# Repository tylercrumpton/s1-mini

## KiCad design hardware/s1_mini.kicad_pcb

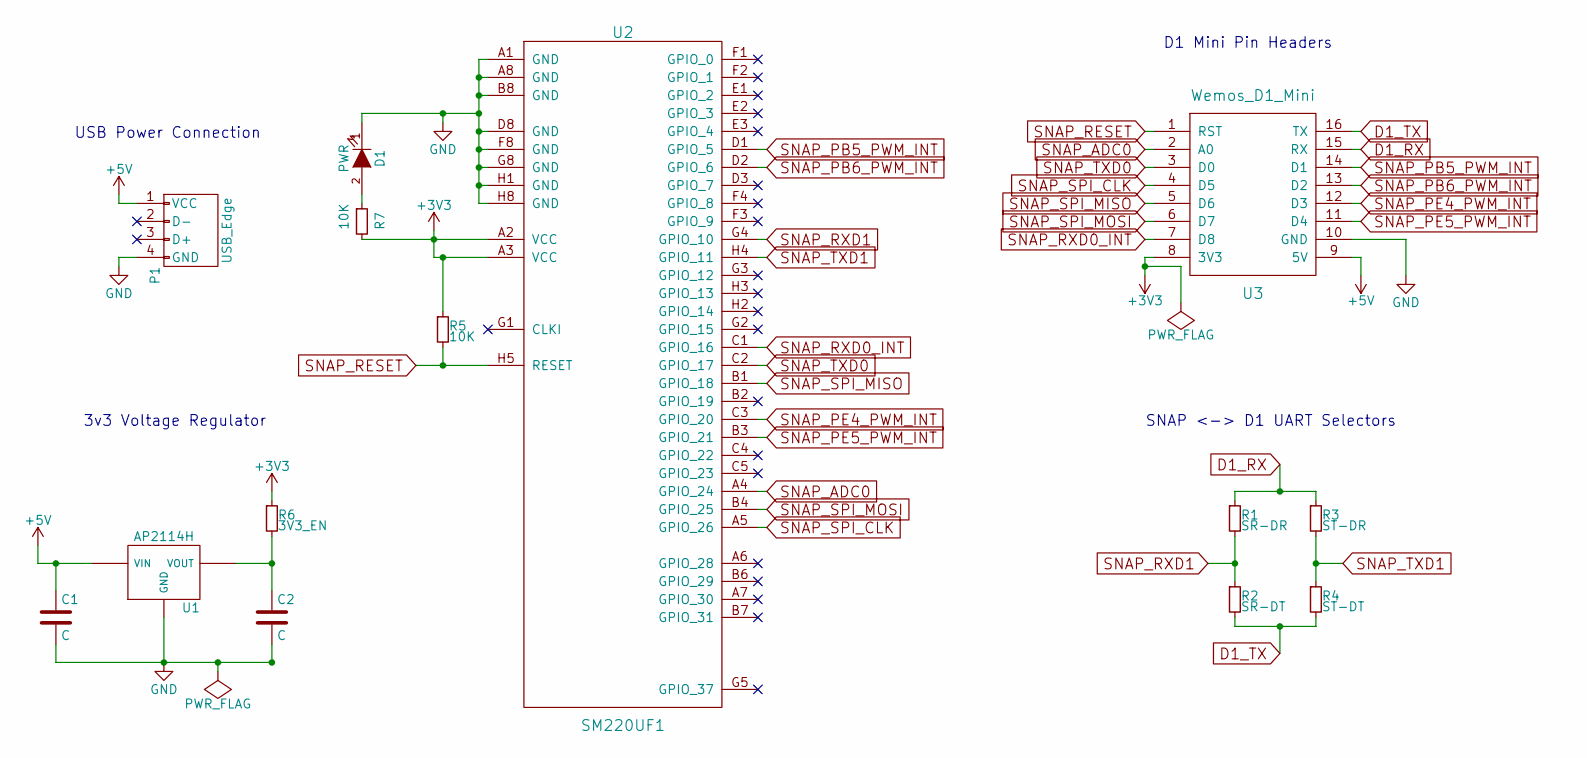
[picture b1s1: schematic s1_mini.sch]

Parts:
C1, C2: C; C_0805_HandSoldering
D1: PWR; LED_1206
P1: USB_Edge; USB_Board_Edge
R1: SR-DR; R_0805_HandSoldering
R2: SR-DT; R_0805_HandSoldering
R3: ST-DR; R_0805_HandSoldering
R4: ST-DT; R_0805_HandSoldering
R5, R7: 10K; R_0805_HandSoldering
R6: 3V3_EN; R_0805_HandSoldering
U1: AP2114H; SOT-223
U2: SM220UF1; SM200
U3: Wemos_D1_Mini; D1_mini

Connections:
+3V3: R5.1, R6.1, R7.2, U2.A2 (VCC), U2.A3 (VCC), U3.8 (3V3)
+5V: C1.1, P1.1 (VCC), U1.3 (VIN), U3.9 (5V)
D1_RX: R1.1, R3.1, U3.15 (RX)
D1_TX: R2.2, R4.2, U3.16 (TX)
GND: C1.2, C2.2, D1.1 (K), P1.4 (GND), U1.1 (GND), U2.A1 (GND), U2.A8 (GND), U2.B8 (GND), U2.D8 (GND), U2.F8 (GND), U2.G8 (GND), U2.H1 (GND), U2.H8 (GND), U3.10 (GND)
unnamed: C2.1, R6.2, U1.2 (VOUT)
unnamed: D1.2 (A), R7.1
SNAP_ADC0: U2.A4 (GPIO_24), U3.2 (A0)
SNAP_PB5_PWM_INT: U2.D1 (GPIO_5), U3.14 (D1)
SNAP_PB6_PWM_INT: U2.D2 (GPIO_6), U3.13 (D2)
SNAP_PE4_PWM_INT: U2.C3 (GPIO_20), U3.12 (D3)
SNAP_PE5_PWM_INT: U2.B3 (GPIO_21), U3.11 (D4)
SNAP_RESET: R5.2, U2.H5 (RESET), U3.1 (RST)
SNAP_RXD0_INT: U2.C1 (GPIO_16), U3.7 (D8)
SNAP_RXD1: R1.2, R2.1, U2.G4 (GPIO_10)
SNAP_SPI_CLK: U2.A5 (GPIO_26), U3.4 (D5)
SNAP_SPI_MISO: U2.B1 (GPIO_18), U3.5 (D6)
SNAP_SPI_MOSI: U2.B4 (GPIO_25), U3.6 (D7)
SNAP_TXD0: U2.C2 (GPIO_17), U3.3 (D0)
SNAP_TXD1: R3.2, R4.1, U2.H4 (GPIO_11)

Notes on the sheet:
USB Power Connection
3v3 Voltage Regulator
D1 Mini Pin Headers
SNAP <-> D1 UART Selectors

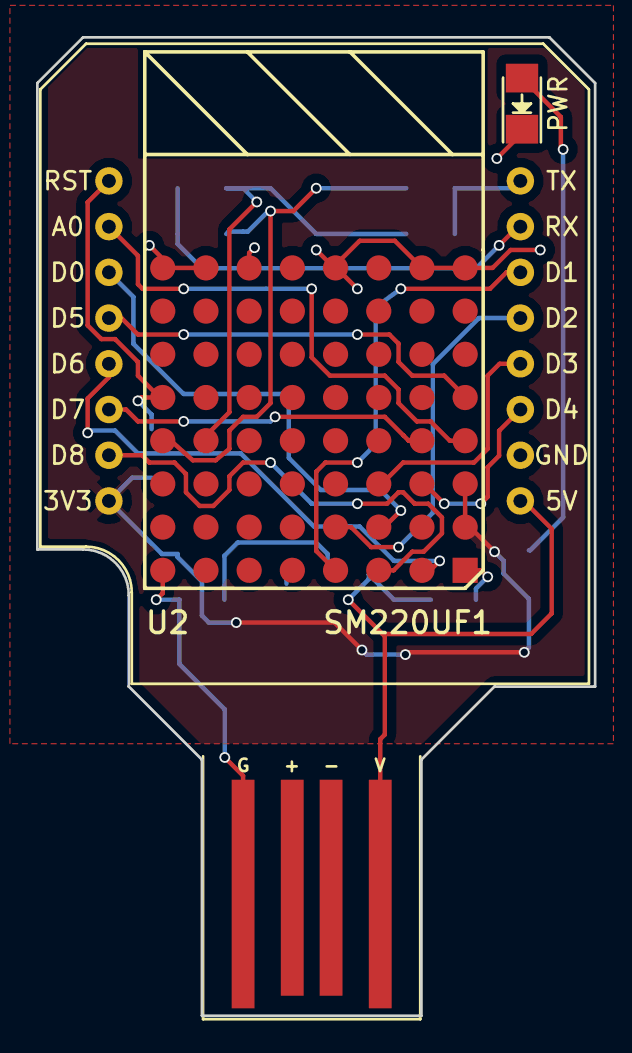
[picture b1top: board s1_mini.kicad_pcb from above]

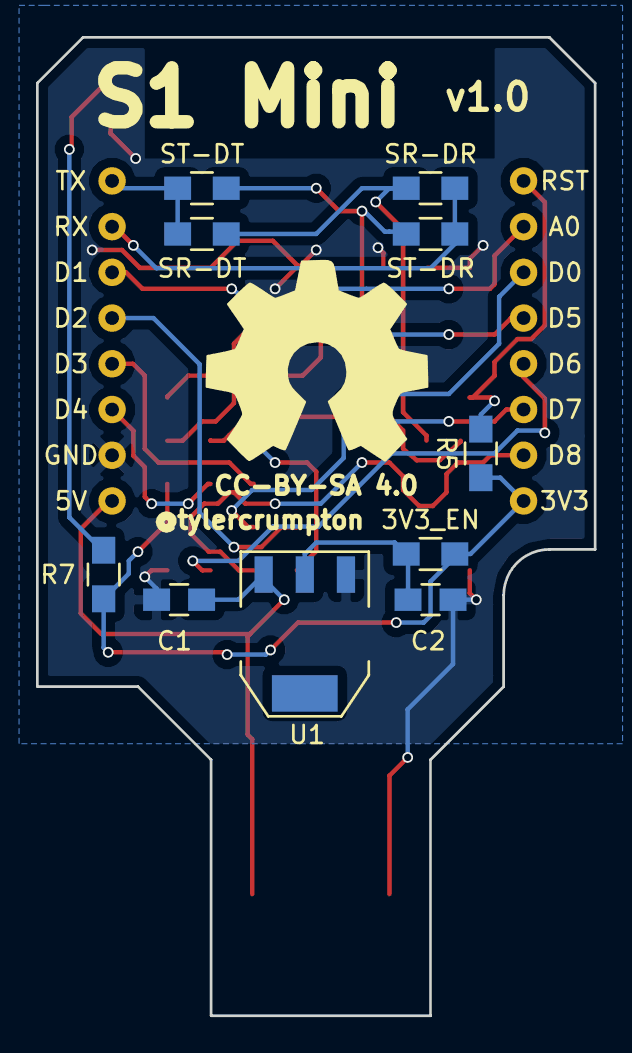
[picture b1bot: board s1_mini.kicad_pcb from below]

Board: 2 copper layers, 31.0 x 54.4 mm, 14 parts (10 on the bottom side), 20 nets.

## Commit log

2016-08-30 Set up the repo.
2016-08-30 Include external resources.
2016-08-30 Update CrumpSchemes submod for USB connector.
2016-08-30 Update CrumpSchemes submod for D1 Mini.
2016-08-30 Add schematic capture.
2016-08-30 Start to assign parts to footprints.
2016-08-30 Annotate parts.
2016-08-31 Add power select resistor.
2016-08-31 Update CrumpSchemes for D1 mini fix.
2016-08-31 Updated CrumpPrints to get d1 mini fix.
2016-08-31 Place parts.
2016-08-31 Clean up part placements.
2016-08-31 Add power LED.
2016-08-31 Route and finish up board.
2016-09-08 Add SNAPpy pin definitions.
2016-09-08 Add relay library.
2016-09-08 Remove relative import from relay lib.
2016-09-08 Add button lib.

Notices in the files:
hardware/s1_mini.kicad_pcb:
CC-BY-SA 4.0
